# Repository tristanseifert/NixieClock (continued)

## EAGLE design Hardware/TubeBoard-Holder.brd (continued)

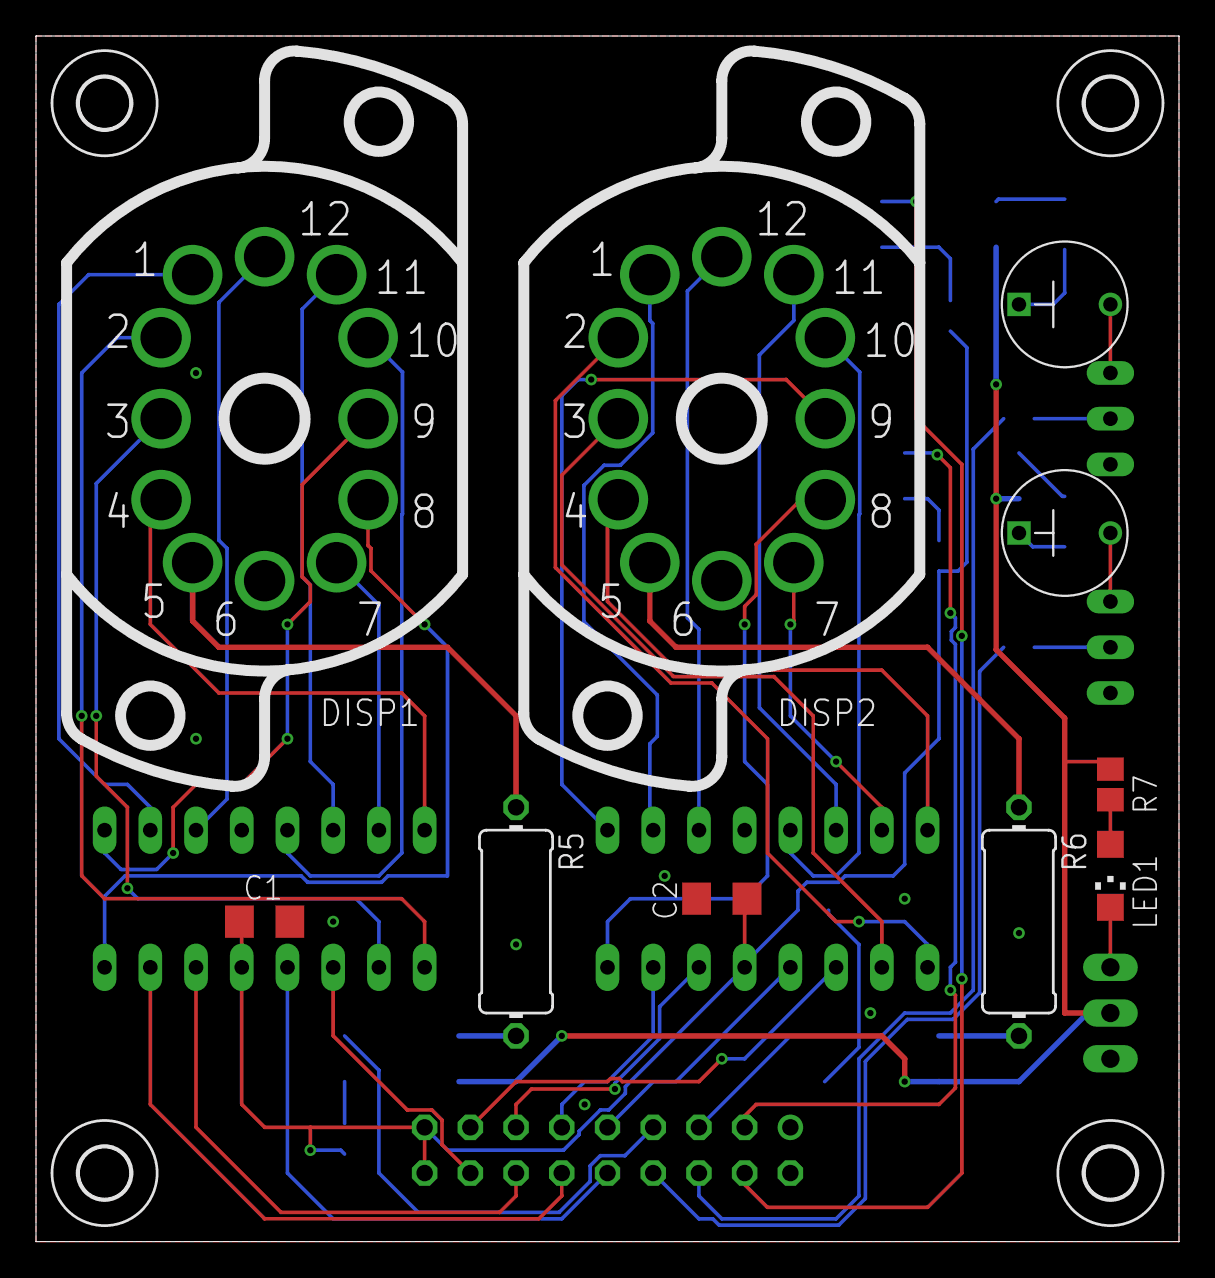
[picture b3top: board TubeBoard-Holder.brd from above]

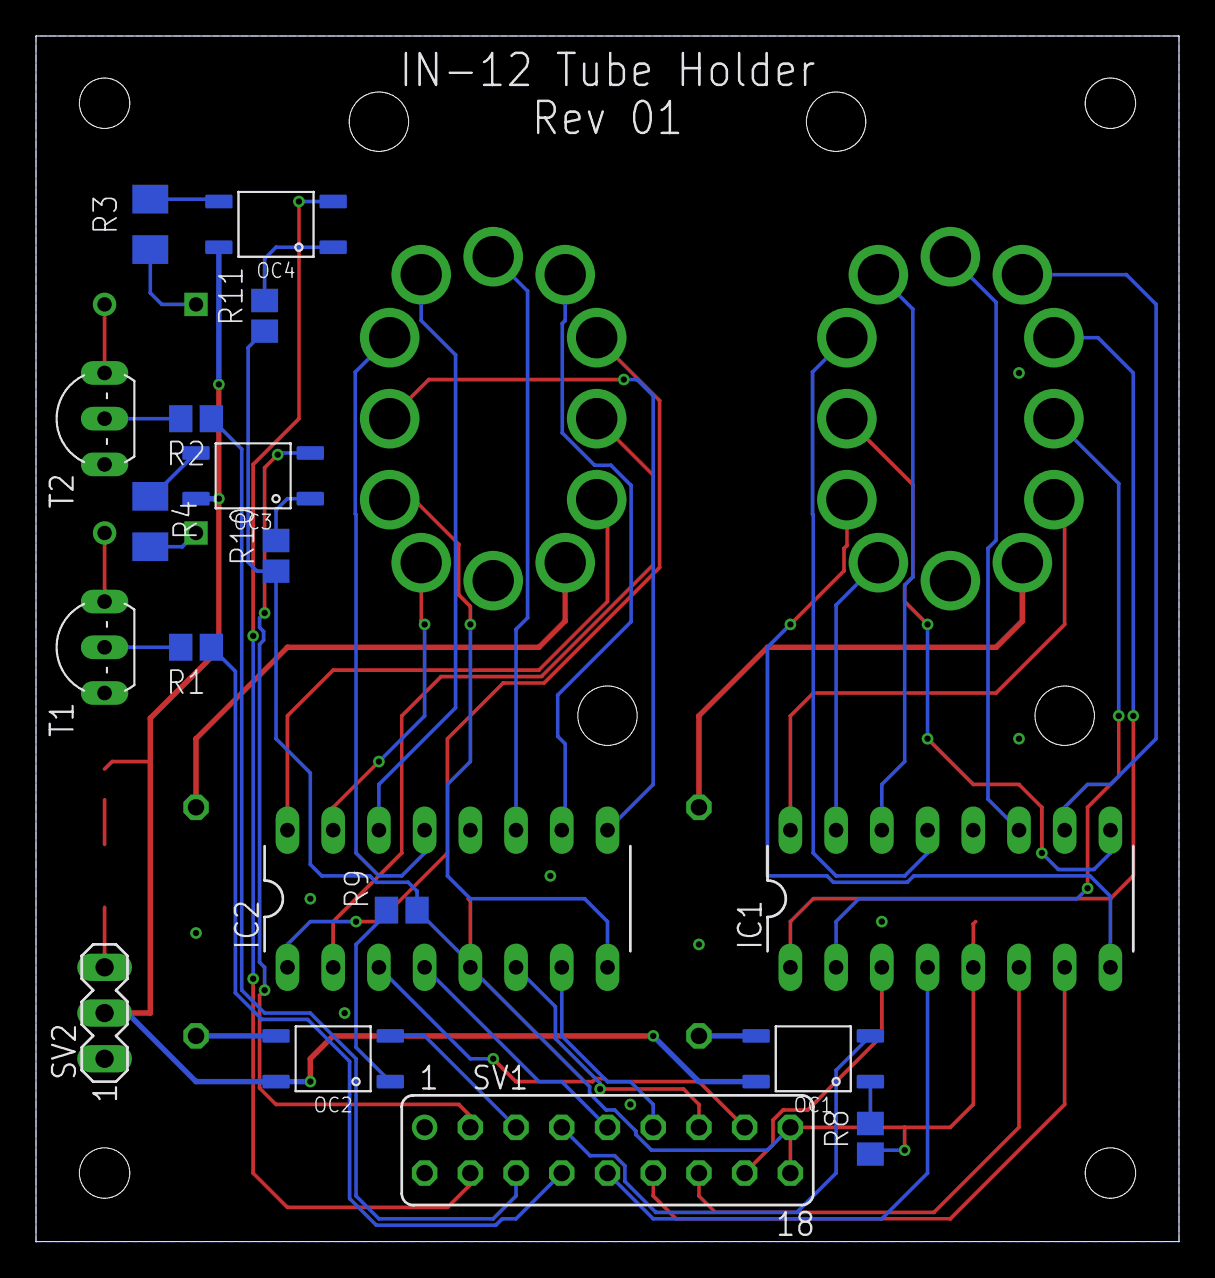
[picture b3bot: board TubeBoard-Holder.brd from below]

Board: 2 copper layers, 63.5 x 67.0 mm, 32 parts (18 on the bottom side), 54 nets.

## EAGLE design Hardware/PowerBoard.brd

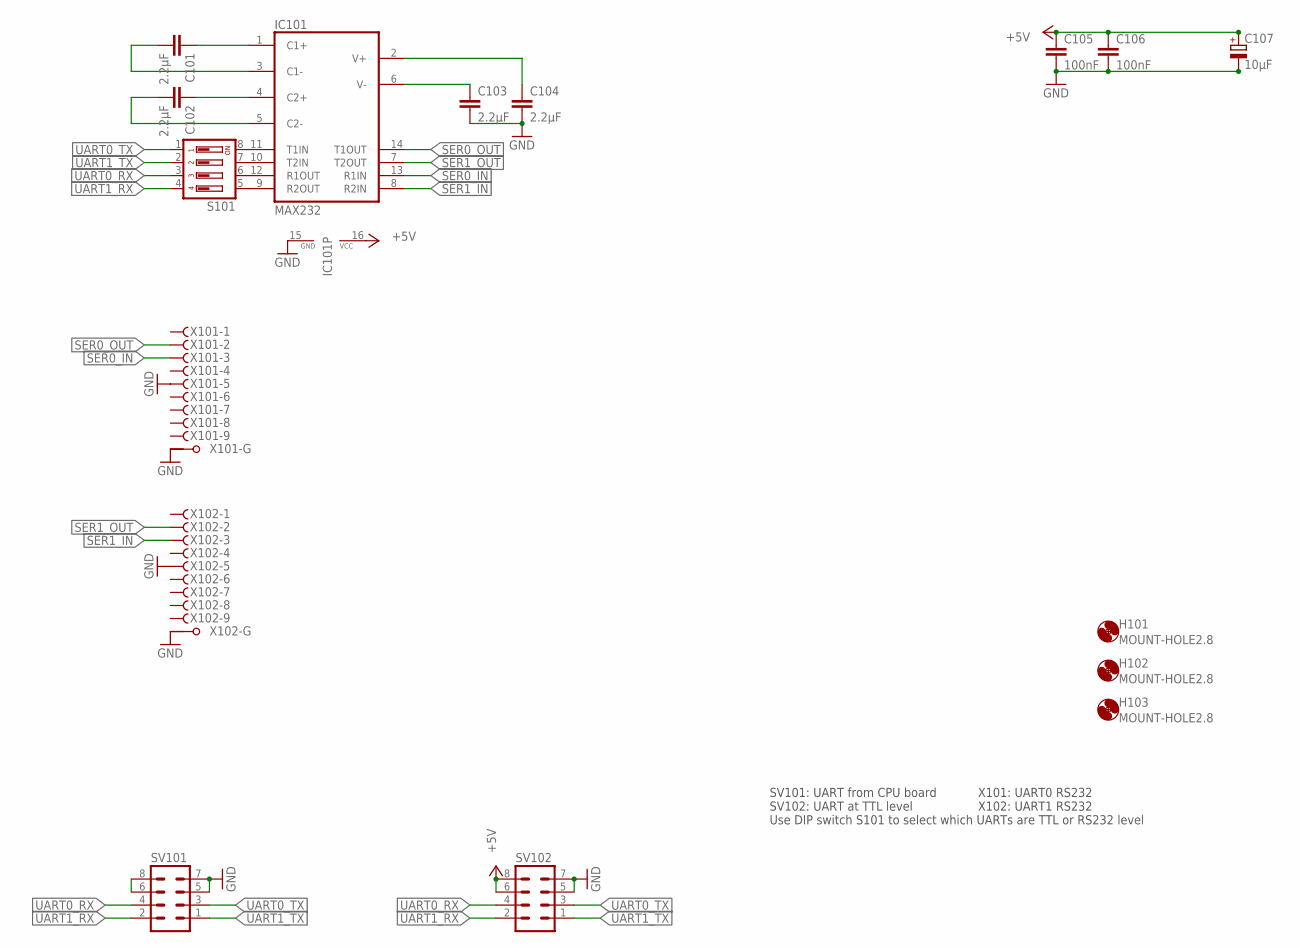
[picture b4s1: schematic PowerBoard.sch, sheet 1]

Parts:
C101, C102, C103, C104: 2.2µF; C0805; MOUSER 710-885012107016
C105, C106: 100nF; C0805; MOUSER 710-885012207072
C107: 10µF; SMC_B; MOUSER 581-TAJB106K020RNJV
H101, H102, H103: MOUNT-HOLE2.8; 2,8
IC101: MAX232; DIL16; MOUSER 595-MAX232N
S101: DP04; DP-04; MOUSER 611-BDB04
SV101, SV102: MA04-2
X101, X102: F09HPS; F09HP

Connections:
+5V: C105.1, C106.1, C107.+, IC101.16 (VCC), SV102.6, SV102.8; also elsewhere on the board
GND: C103.2, C104.2, C105.2, C106.2, C107.-, IC101.15 (GND), SV101.5, SV101.7, SV102.5, SV102.7, X101.5 (F), X101.G1, X102.5 (F), X102.G1; also elsewhere on the board
unnamed: C104.1, IC101.2 (V+)
unnamed: C103.1, IC101.6 (V-)
unnamed: C102.1, IC101.4 (C2+)
unnamed: C101.1, IC101.1 (C1+)
unnamed: SV101.6, SV101.8
unnamed: IC101.9 (R2OUT), S101.5
unnamed: C102.2, IC101.5 (C2-)
unnamed: C101.2, IC101.3 (C1-)
unnamed: IC101.12 (R1OUT), S101.6
unnamed: IC101.10 (T2IN), S101.7
unnamed: IC101.11 (T1IN), S101.8
SER0_IN: IC101.13 (R1IN), X101.3 (F)
SER0_OUT: IC101.14 (T1OUT), X101.2 (F)
SER1_IN: IC101.8 (R2IN), X102.3 (F)
SER1_OUT: IC101.7 (T2OUT), X102.2 (F)
UART0_RX: S101.3, SV101.4, SV102.4
UART0_TX: S101.1, SV101.3, SV102.3
UART1_RX: S101.4, SV101.2, SV102.2
UART1_TX: S101.2, SV101.1, SV102.1

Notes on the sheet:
X101: UART0 RS232 X102: UART1 RS232
SV101: UART from CPU board SV102: UART at TTL level Use DIP switch S101 to select which UARTs are TTL or RS232 level

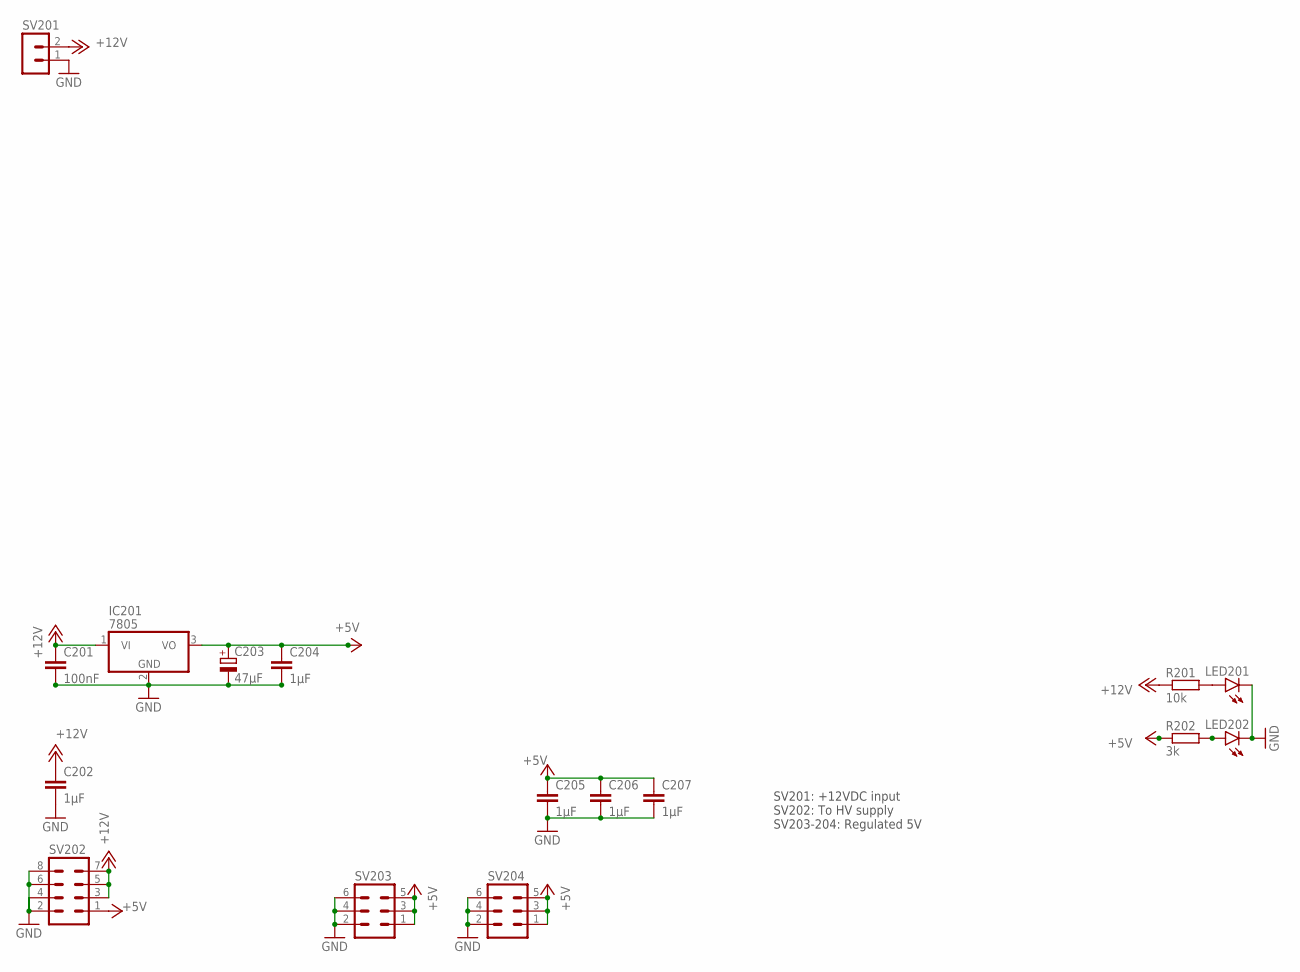
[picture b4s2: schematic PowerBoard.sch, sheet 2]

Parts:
C201: 100nF; C0805; MOUSER 710-885012207072
C202, C204, C205, C206, C207: 1µF; C0805; MOUSER 710-885012107015
C203: 47µF; CT6032; MOUSER 581-TAJD476M016RNJV
IC201: 7805; TO220V; MOUSER 490-VXO7805-1000
LED201, LED202: LEDCHIPLED_1206; CHIPLED_1206; MOUSER 710-156120YS75300
R201: 10k; R2012; MOUSER 652-CR0805FX-1002ELF
R202: 3k; R2012; MOUSER 652-CR0805JW-302ELF
SV201: 1792863
SV202: MA04-2
SV203, SV204: MA03-2

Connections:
+5V: C203.+, C204.1, C205.1, C206.1, C207.1, IC201.3 (VO), R202.1, SV202.1, SV203.1, SV203.3, SV203.5, SV204.1, SV204.3, SV204.5; also elsewhere on the board
+12V: C201.1, C202.1, IC201.1 (VI), R201.1, SV201.2, SV202.3, SV202.5, SV202.7
GND: C201.2, C202.2, C203.-, C204.2, C205.2, C206.2, C207.2, IC201.2 (GND), LED201.C, LED202.C, SV201.1, SV202.2, SV202.4, SV202.6, SV202.8, SV203.2, SV203.4, SV203.6, SV204.2, SV204.4, SV204.6; also elsewhere on the board
unnamed: LED202.A, R202.2
unnamed: LED201.A, R201.2

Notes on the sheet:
SV201: +12VDC input SV202: To HV supply SV203-204: Regulated 5V

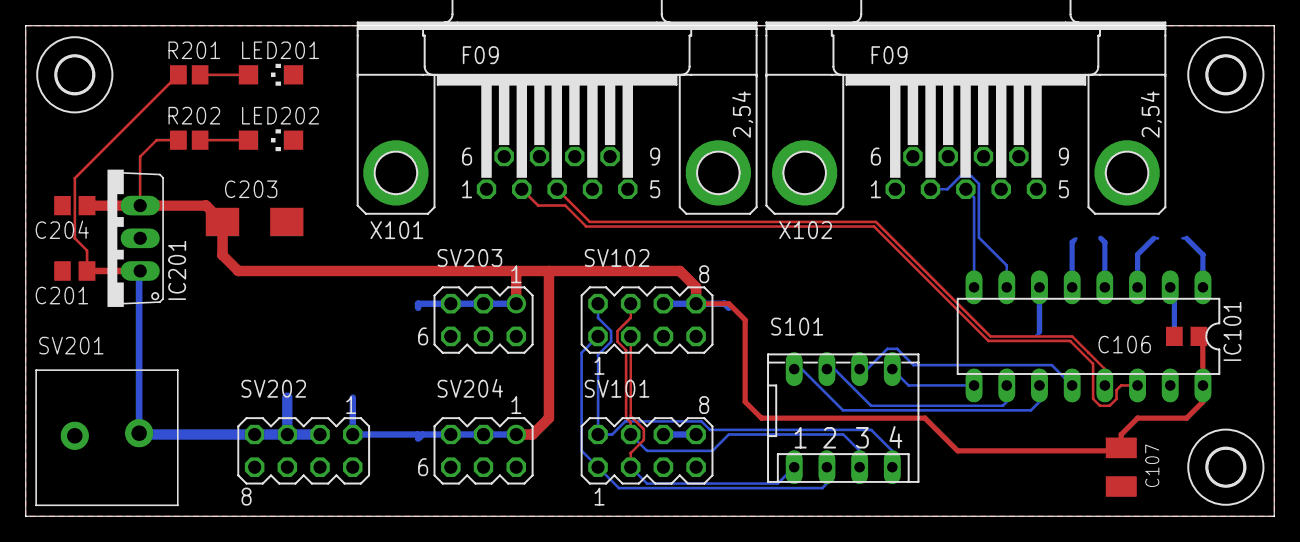
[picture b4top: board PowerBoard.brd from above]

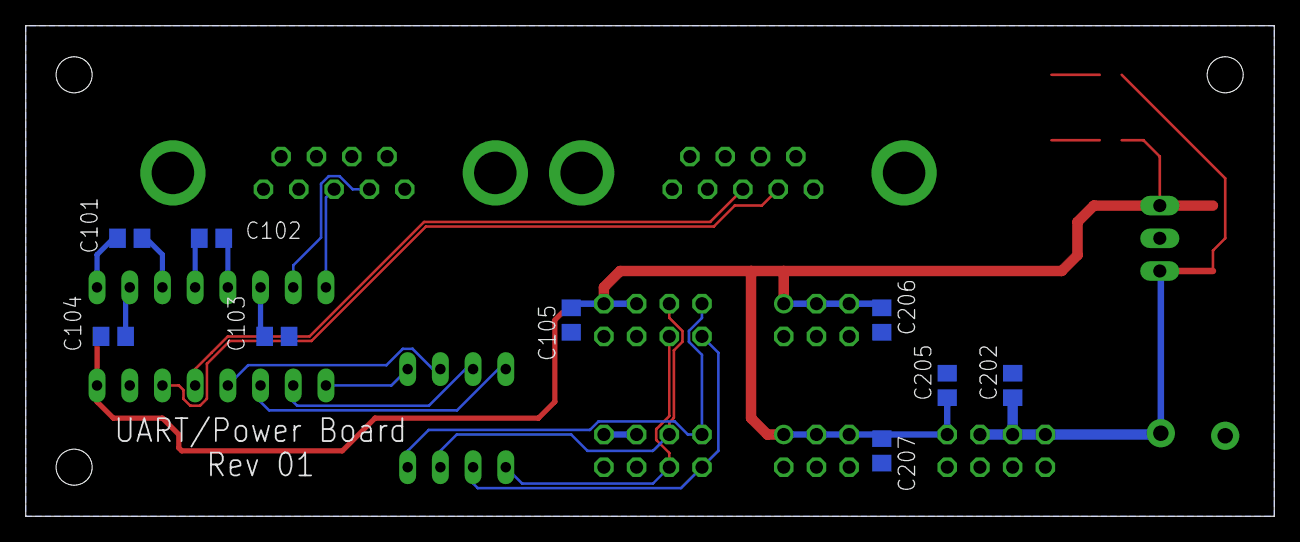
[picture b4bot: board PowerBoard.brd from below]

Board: 2 copper layers, 97.0 x 38.1 mm, 32 parts (9 on the bottom side), 24 nets.

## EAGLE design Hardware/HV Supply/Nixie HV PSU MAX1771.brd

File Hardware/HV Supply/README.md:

# Nixie Clock HV Supply
This power supply is based on Nick de Smith's [Nixie HV Switching PSU](https://www.desmith.net/NMdS/Electronics/NixiePSU.html) and derived from the provided EAGLE files. Modifications were made to use different connectors, and to add Mouser part numbers.

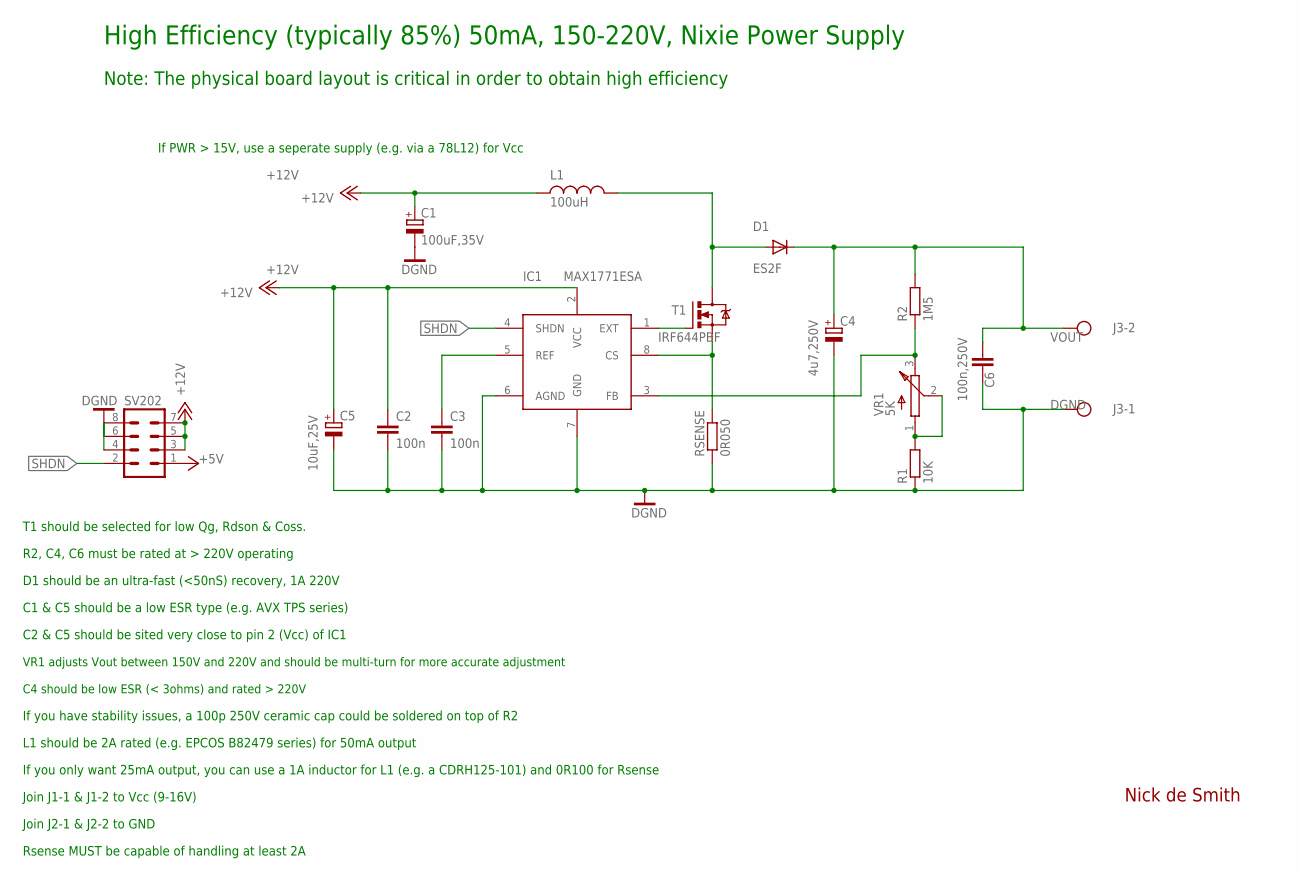
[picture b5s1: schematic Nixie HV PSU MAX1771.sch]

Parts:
C1: 100uF,35V; C-EIA-7343; MOUSER 581-TPSD107M020R0085
C2, C3: 100n; C0805; MOUSER 80-C0805C104M4V
C4: 4u7,250V; NICHICON-UJ-12; MOUSER 667-EEV-EB2E100Q
C5: 10uF,25V; C-EIA-7343; MOUSER 581-TPSD106K035R0300
C6: 100n,250V; C2420; MOUSER 667-ECW-U2104KC9
D1: ES2F; SMC; MOUSER 821-ES2FR5
IC1: MAX1771ESA; SO-8; MOUSER 700-MAX1771ESAT
J3: TERM-BLOCK-2-02IN; SCREW-2-02
L1: 100uH; L-B82479; MOUSER 871-B82479A1104M
R1: 10K; R0805; MOUSER 71-CRCW080510K0FKEAC
R2: 1M5; R2512; MOUSER 279-35221M5JT
RSENSE: 0R050; R2010; MOUSER 66-LR2010LF-01-R050
SV202: MA04-2
T1: IRF644PBF; TO220BV; MOUSER 844-IRF644PBF
VR1: 5K; BOURNS-3214W; MOUSER 652-3214W-1-502E

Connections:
+5V: SV202.1
+12V: C1.+, C2.1, C5.+, IC1.2 (VCC), L1.P$1 (1), SV202.3, SV202.5, SV202.7
DGND: C1.-, C2.2, C3.2, C4.1 (-), C5.-, C6.P$2 (2), IC1.6 (AGND), IC1.7 (GND), J3.1, R1.1, RSENSE.1, SV202.4, SV202.6, SV202.8
EXT: IC1.1 (EXT), T1.G
unnamed: IC1.8 (CS), RSENSE.2, T1.S
unnamed: R1.2, VR1.1 (A), VR1.2 (W)
unnamed: IC1.3 (FB), R2.1, VR1.3 (B)
unnamed: D1.A, L1.P$2 (2), T1.D
unnamed: C3.1, IC1.5 (REF)
SHDN: IC1.4 (SHDN), SV202.2
VOUT: C4.2 (+), C6.P$1 (1), D1.C, J3.2, R2.2

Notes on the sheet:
R2, C4, C6 must be rated at > 220V operating
D1 should be an ultra-fast (<50nS) recovery, 1A 220V
C1 & C5 should be a low ESR type (e.g. AVX TPS series)
C2 & C5 should be sited very close to pin 2 (Vcc) of IC1
Nick de Smith
VR1 adjusts Vout between 150V and 220V and should be multi-turn for more accurate adjustment
C4 should be low ESR (< 3ohms) and rated > 220V
If you have stability issues, a 100p 250V ceramic cap could be soldered on top of R2
L1 should be 2A rated (e.g. EPCOS B82479 series) for 50mA output
Join J1-1 & J1-2 to Vcc (9-16V)
Join J2-1 & J2-2 to GND
T1 should be selected for low Qg, Rdson & Coss.
Rsense MUST be capable of handling at least 2A
High Efficiency (typically 85%) 50mA, 150-220V, Nixie Power Supply
If PWR > 15V, use a seperate supply (e.g. via a 78L12) for Vcc
Note: The physical board layout is critical in order to obtain high efficiency
If you only want 25mA output, you can use a 1A inductor for L1 (e.g. a CDRH125-101) and 0R100 for Rsense

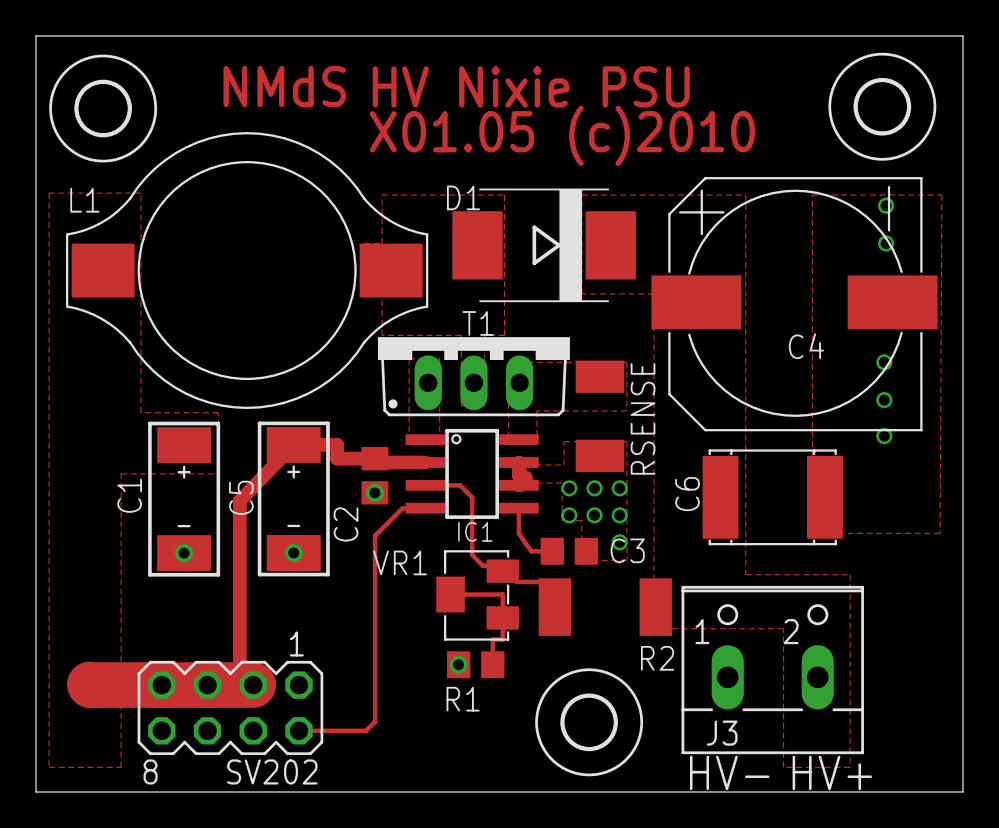
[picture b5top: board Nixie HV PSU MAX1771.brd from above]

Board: 2 copper layers, 51.5 x 42.0 mm, 19 parts (0 on the bottom side), 10 nets.

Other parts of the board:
U$2, U$3, U$4: 2,8

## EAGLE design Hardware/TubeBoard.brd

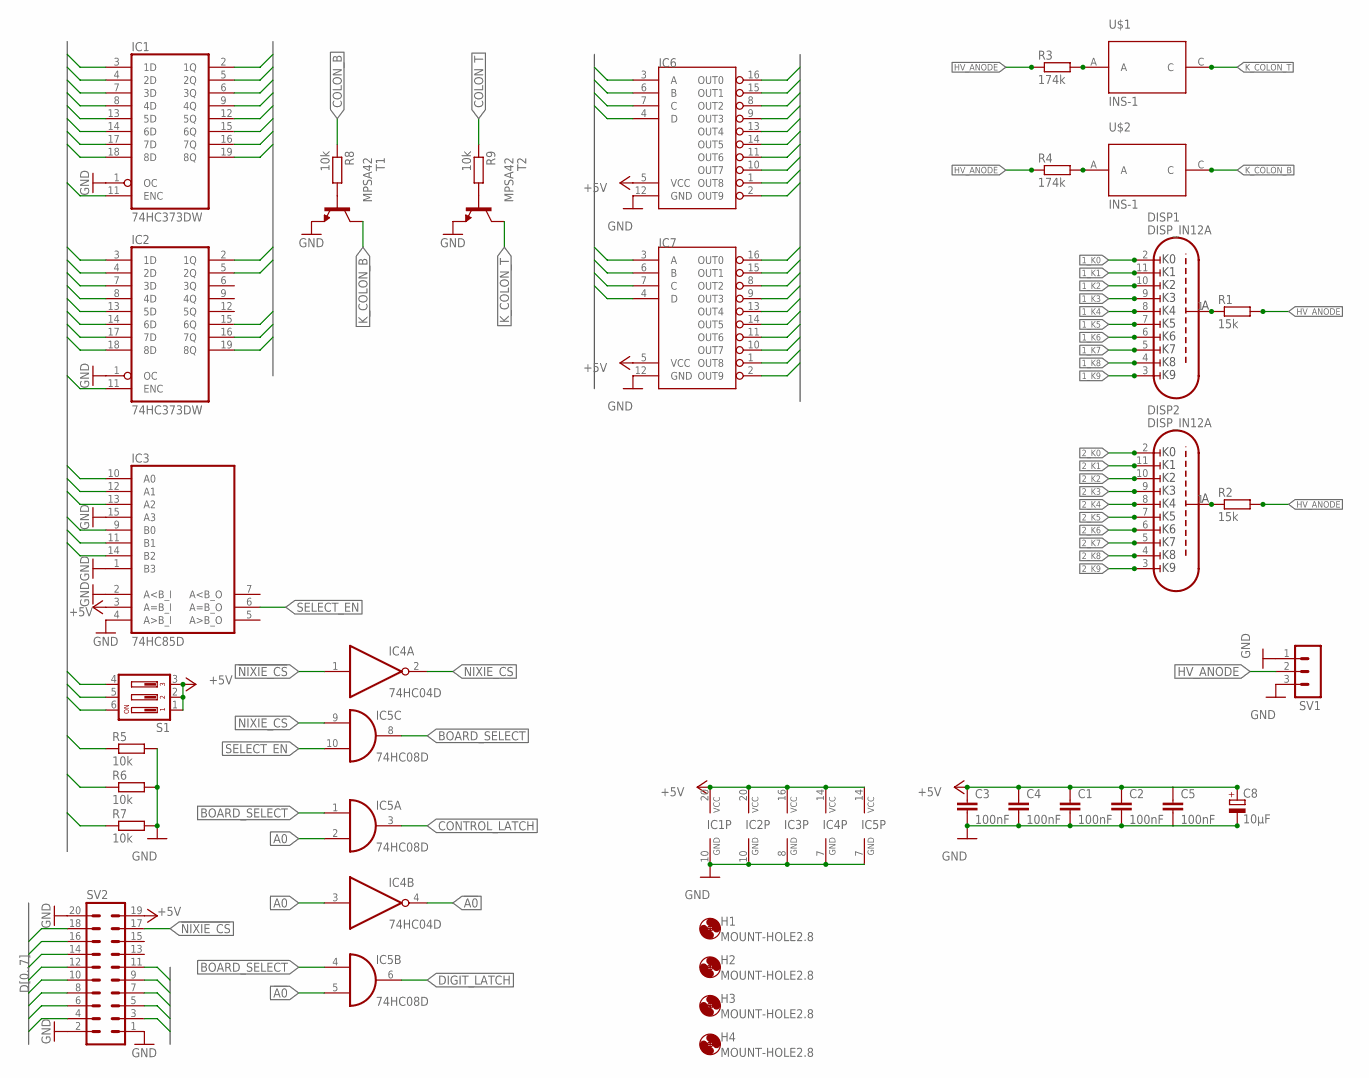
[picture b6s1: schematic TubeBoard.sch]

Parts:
C1, C2, C3, C4, C5: 100nF; C1206
C8: 10µF; SMC_B; MOUSER 581-TAJB106K020RNJV
DISP1, DISP2: DISP_IN12A; DISP_IN-12_SOCKET
H1, H2, H3, H4: MOUNT-HOLE2.8; 2,8
IC1, IC2: 74HC373DW; SO20W
IC3: 74HC85D; SO16; MOUSER 771-74HC85D-T
IC4: 74HC04D; SO14
IC5: 74HC08D; SO14
IC6, IC7: 7441DIL16; DIL16
R1, R2: 15k; 0411/12
R3, R4: 174k; M1206; MOUSER 667-ERJ-8ENF1743V
R5, R6, R7, R8, R9: 10k; R2012; MOUSER 652-CR0805FX-1002ELF
S1: SD4-03; MOUSER 611-BDB03
SV1: MA03-1
SV2: MA10-2
T1, T2: MPSA42; TO92-EBC; MOUSER 833-MPSA42-AP
U$1, U$2: INS-1

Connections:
1_K0: DISP1.2 (K0), IC6.16 (OUT0)
1_K1: DISP1.11 (K1), IC6.15 (OUT1)
1_K2: DISP1.10 (K2), IC6.8 (OUT2)
1_K3: DISP1.9 (K3), IC6.9 (OUT3)
1_K4: DISP1.8 (K4), IC6.13 (OUT4)
1_K5: DISP1.7 (K5), IC6.14 (OUT5)
1_K6: DISP1.6 (K6), IC6.11 (OUT6)
1_K7: DISP1.5 (K7), IC6.10 (OUT7)
1_K8: DISP1.4 (K8), IC6.1 (OUT8)
1_K9: DISP1.3 (K9), IC6.2 (OUT9)
2_K0: DISP2.2 (K0), IC7.16 (OUT0)
2_K1: DISP2.11 (K1), IC7.15 (OUT1)
2_K2: DISP2.10 (K2), IC7.8 (OUT2)
2_K3: DISP2.9 (K3), IC7.9 (OUT3)
2_K4: DISP2.8 (K4), IC7.13 (OUT4)
2_K5: DISP2.7 (K5), IC7.14 (OUT5)
2_K6: DISP2.6 (K6), IC7.11 (OUT6)
2_K7: DISP2.5 (K7), IC7.10 (OUT7)
2_K8: DISP2.4 (K8), IC7.1 (OUT8)
2_K9: DISP2.3 (K9), IC7.2 (OUT9)
!A0: IC4.4 (O), IC5.5 (I1)
!NIXIE_CS: IC4.1 (I), SV2.17
+5V: C1.1, C2.1, C3.1, C4.1, C5.1, C8.+, IC1.20 (VCC), IC2.20 (VCC), IC3.3 (A=B_I), IC3.16 (VCC), IC4.14 (VCC), IC5.14 (VCC), IC6.5 (VCC), IC7.5 (VCC), S1.1, S1.2, S1.3, SV2.19
A0: IC4.3 (I), IC5.2 (I1), SV2.3
A1: SV2.5
A2: IC3.10 (A0), SV2.7
A3: IC3.12 (A1), SV2.9
A4: IC3.13 (A2), SV2.11
BOARD_SELECT: IC5.1 (I0), IC5.4 (I0), IC5.8 (O)
COLON_B: IC2.2 (1Q), R8.1
COLON_T: IC2.5 (2Q), R9.1
CONTROL_LATCH: IC2.11 (ENC), IC5.3 (O)
D0: IC1.3 (1D), IC2.3 (1D), SV2.8
D1: IC1.4 (2D), IC2.4 (2D), SV2.6
D2: IC1.7 (3D), IC2.7 (3D), SV2.4
D3: IC1.8 (4D), IC2.8 (4D), SV2.10
D4: IC1.13 (5D), IC2.13 (5D), SV2.12
D5: IC1.14 (6D), IC2.14 (6D), SV2.14
D6: IC1.17 (7D), IC2.17 (7D), SV2.16
D7: IC1.18 (8D), IC2.18 (8D), SV2.18
DIGIT_LATCH: IC1.11 (ENC), IC5.6 (O)
DRIVE_HI: IC2.19 (8Q)
DRIVE_LO: IC2.15 (6Q)
DRIVE_MED: IC2.16 (7Q)
GND: C1.2, C2.2, C3.2, C4.2, C5.2, C8.-, IC1.1 (OC), IC1.10 (GND), IC2.1 (OC), IC2.10 (GND), IC3.1 (B3), IC3.2 (A<B_I), IC3.4 (A>B_I), IC3.8 (GND), IC3.15 (A3), IC4.7 (GND), IC5.7 (GND), IC6.12 (GND), IC7.12 (GND), R5.2, R6.2, R7.2, SV1.1, SV1.3, SV2.1, SV2.2, SV2.20, T1.E, T2.E
HV_ANODE: R1.2, R2.2, R3.1, R4.1, SV1.2
ID0: IC3.9 (B0), R7.1, S1.6
ID1: IC3.11 (B1), R6.1, S1.5
ID2: IC3.14 (B2), R5.1, S1.4
K_COLON_B: T1.C, U$2.C
K_COLON_T: T2.C, U$1.C
LDIGIT0: IC1.2 (1Q), IC6.3 (A)
LDIGIT1: IC1.5 (2Q), IC6.6 (B)
LDIGIT2: IC1.6 (3Q), IC6.7 (C)
LDIGIT3: IC1.9 (4Q), IC6.4 (D)
unnamed: DISP1.1 (ANODE), R1.1
unnamed: DISP2.1 (ANODE), R2.1
unnamed: R3.2, U$1.A
unnamed: R4.2, U$2.A
unnamed: R8.2, T1.B
unnamed: R9.2, T2.B
NIXIE_CS: IC4.2 (O), IC5.9 (I0)
RDIGIT0: IC1.12 (5Q), IC7.3 (A)
RDIGIT1: IC1.15 (6Q), IC7.6 (B)
RDIGIT2: IC1.16 (7Q), IC7.7 (C)
RDIGIT3: IC1.19 (8Q), IC7.4 (D)
SELECT_EN: IC3.6 (A=B_O), IC5.10 (I1)

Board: 2 copper layers, 35 parts (4 on the bottom side), 63 nets, no tracks yet.

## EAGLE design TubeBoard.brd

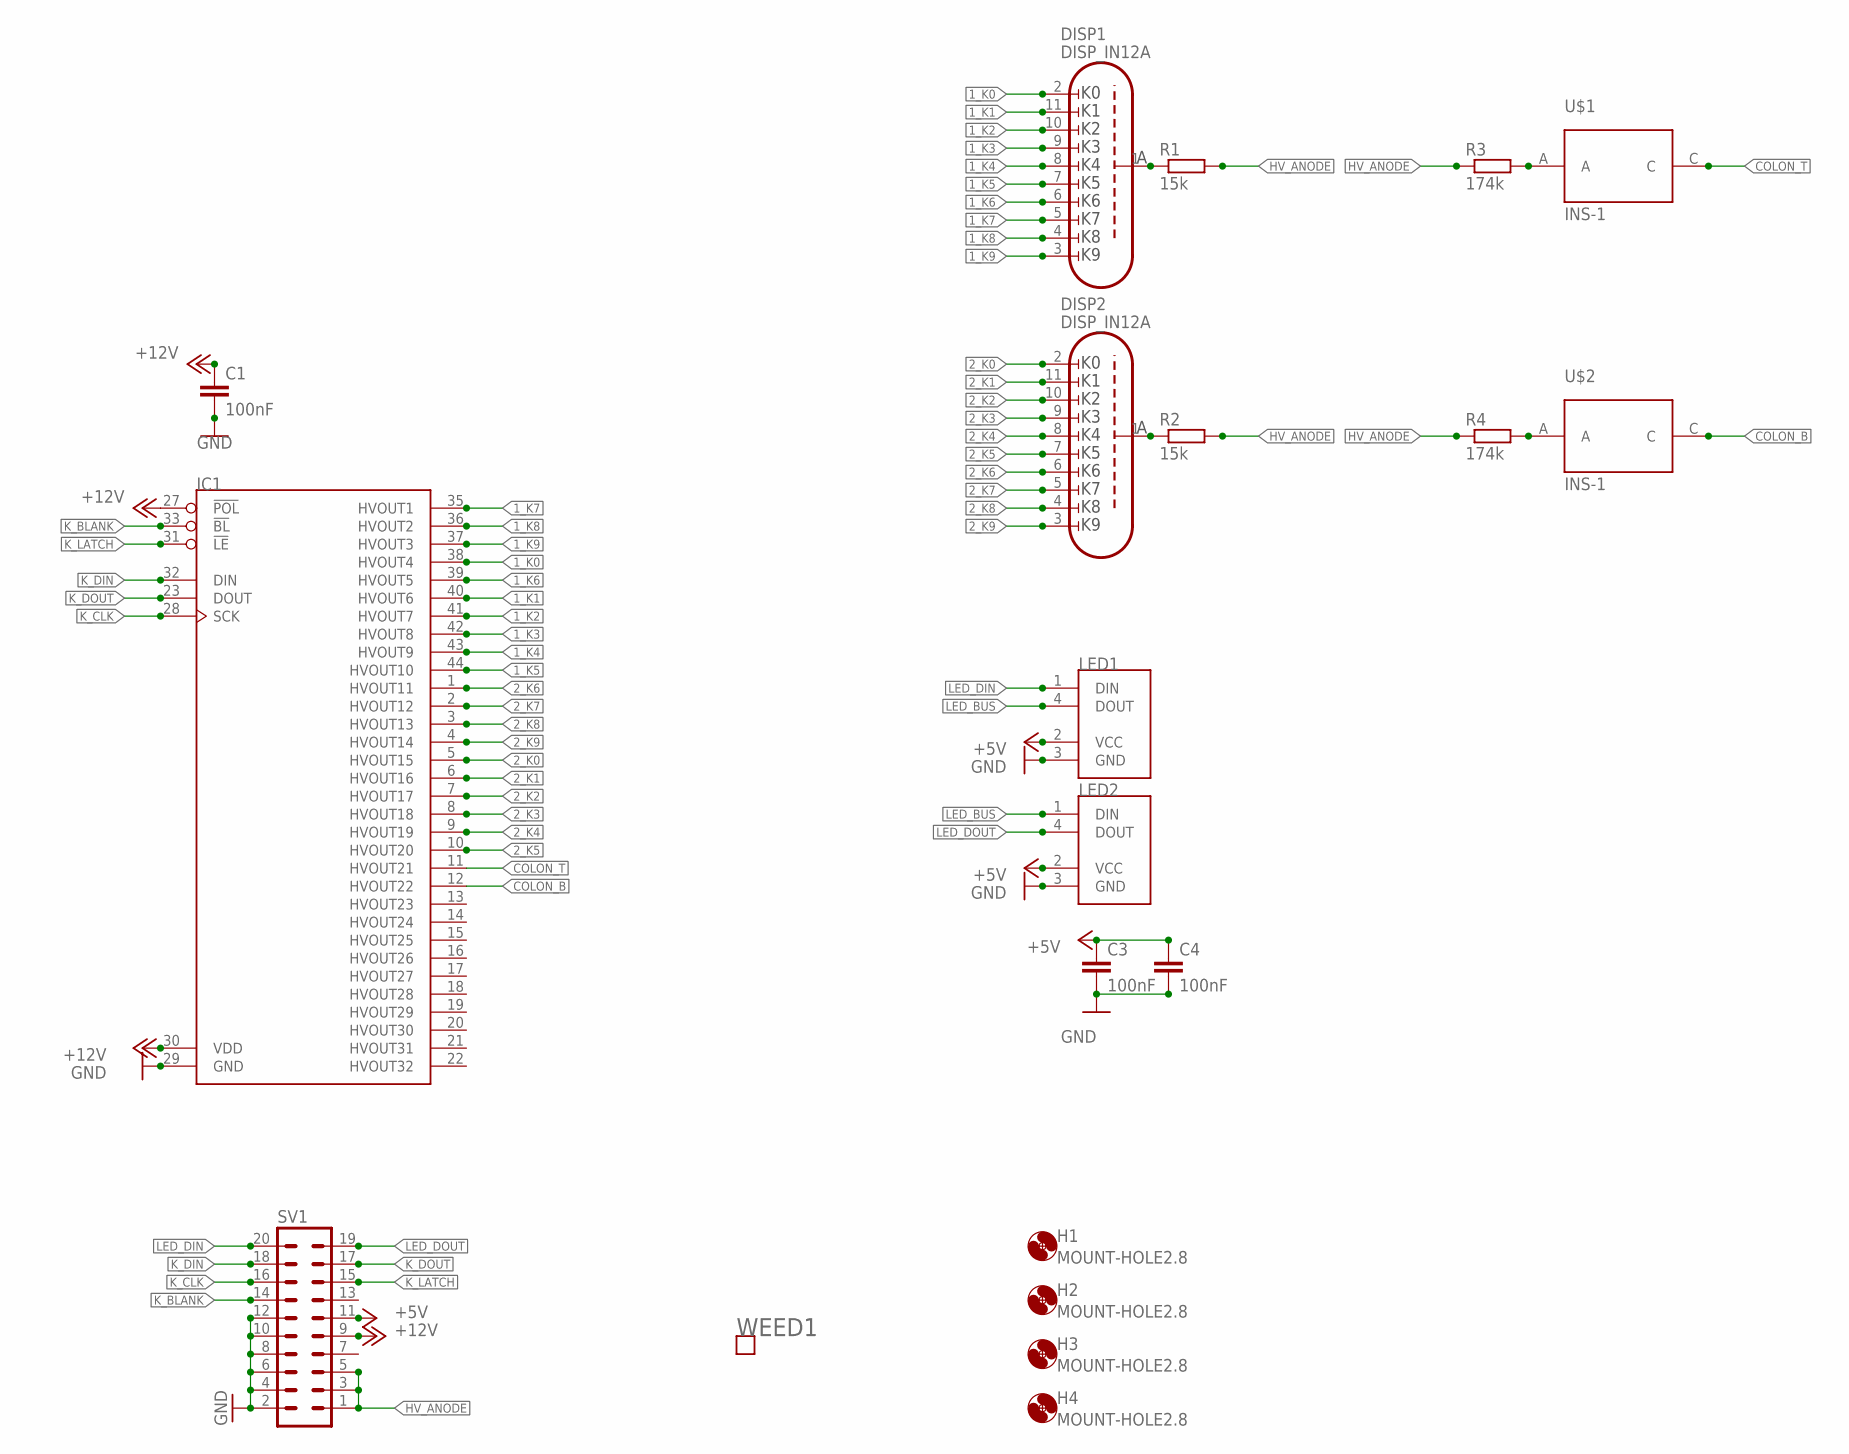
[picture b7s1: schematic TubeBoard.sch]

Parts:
C1, C3, C4: 100nF; C1206
DISP1, DISP2: DISP_IN12A; DISP_IN-12_SOCKET
H1, H2, H3, H4: MOUNT-HOLE2.8; 2,8
IC1: HV5530PQFP-44; PQFP44
LED1, LED2: NEOPIXEL-5MMLED-4PIN; LED5MMRGB
R1, R2: 15k; 0411/12
R3, R4: 174k; M1206; MOUSER 667-ERJ-8ENF1743V
SV1: MA10-2
U$1, U$2: INS-1
WEED1: WEED; DOINK

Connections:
1_K0: DISP1.2 (K0), IC1.38 (HVOUT4)
1_K1: DISP1.11 (K1), IC1.40 (HVOUT6)
1_K2: DISP1.10 (K2), IC1.41 (HVOUT7)
1_K3: DISP1.9 (K3), IC1.42 (HVOUT8)
1_K4: DISP1.8 (K4), IC1.43 (HVOUT9)
1_K5: DISP1.7 (K5), IC1.44 (HVOUT10)
1_K6: DISP1.6 (K6), IC1.39 (HVOUT5)
1_K7: DISP1.5 (K7), IC1.35 (HVOUT1)
1_K8: DISP1.4 (K8), IC1.36 (HVOUT2)
1_K9: DISP1.3 (K9), IC1.37 (HVOUT3)
2_K0: DISP2.2 (K0), IC1.5 (HVOUT15)
2_K1: DISP2.11 (K1), IC1.6 (HVOUT16)
2_K2: DISP2.10 (K2), IC1.7 (HVOUT17)
2_K3: DISP2.9 (K3), IC1.8 (HVOUT18)
2_K4: DISP2.8 (K4), IC1.9 (HVOUT19)
2_K5: DISP2.7 (K5), IC1.10 (HVOUT20)
2_K6: DISP2.6 (K6), IC1.1 (HVOUT11)
2_K7: DISP2.5 (K7), IC1.2 (HVOUT12)
2_K8: DISP2.4 (K8), IC1.3 (HVOUT13)
2_K9: DISP2.3 (K9), IC1.4 (HVOUT14)
!K_BLANK: IC1.33 (!BL), SV1.14
!K_LATCH: IC1.31 (!LE), SV1.15
+5V: C3.1, C4.1, LED1.2 (VCC), LED2.2 (VCC), SV1.11
+12V: C1.1, IC1.27 (!POL), IC1.30 (VDD), SV1.9
COLON_B: IC1.12 (HVOUT22), U$2.C
COLON_T: IC1.11 (HVOUT21), U$1.C
GND: C1.2, C3.2, C4.2, IC1.29 (GND), LED1.3 (GND), LED2.3 (GND), SV1.2, SV1.4, SV1.6, SV1.8, SV1.10, SV1.12
HV_ANODE: R1.2, R2.2, R3.1, R4.1, SV1.1, SV1.3, SV1.5
K_CLK: IC1.28 (SCK), SV1.16
K_DIN: IC1.32 (DIN), SV1.18
K_DOUT: IC1.23 (DOUT), SV1.17
LED_BUS: LED1.4 (DOUT), LED2.1 (DIN)
LED_DIN: LED1.1 (DIN), SV1.20
LED_DOUT: LED2.4 (DOUT), SV1.19
unnamed: DISP1.1 (ANODE), R1.1
unnamed: DISP2.1 (ANODE), R2.1
unnamed: R3.2, U$1.A
unnamed: R4.2, U$2.A

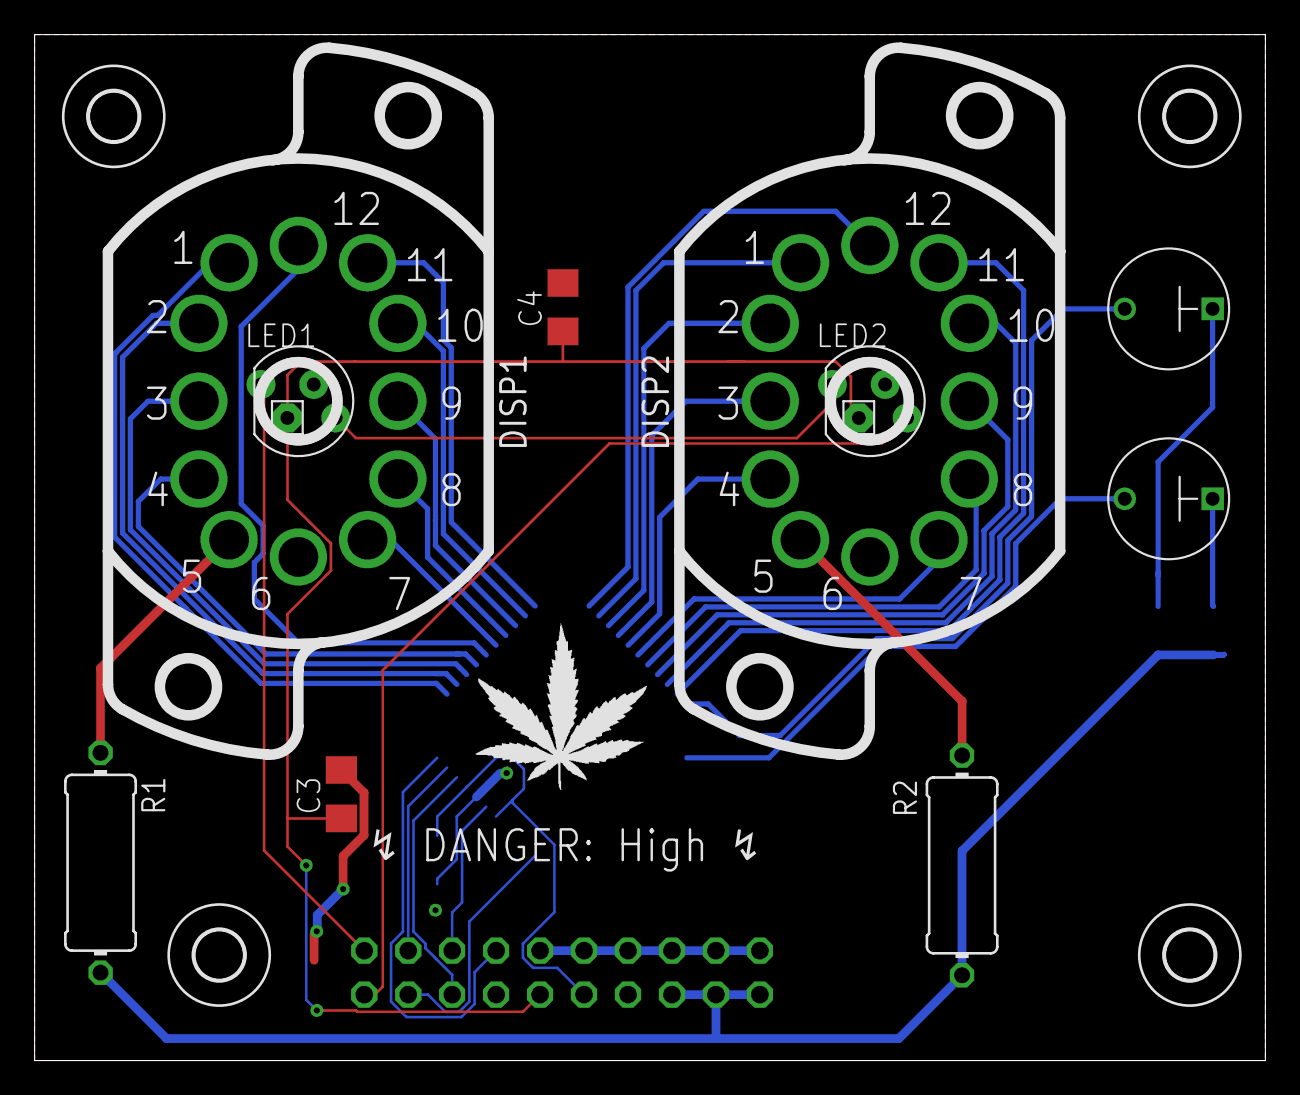
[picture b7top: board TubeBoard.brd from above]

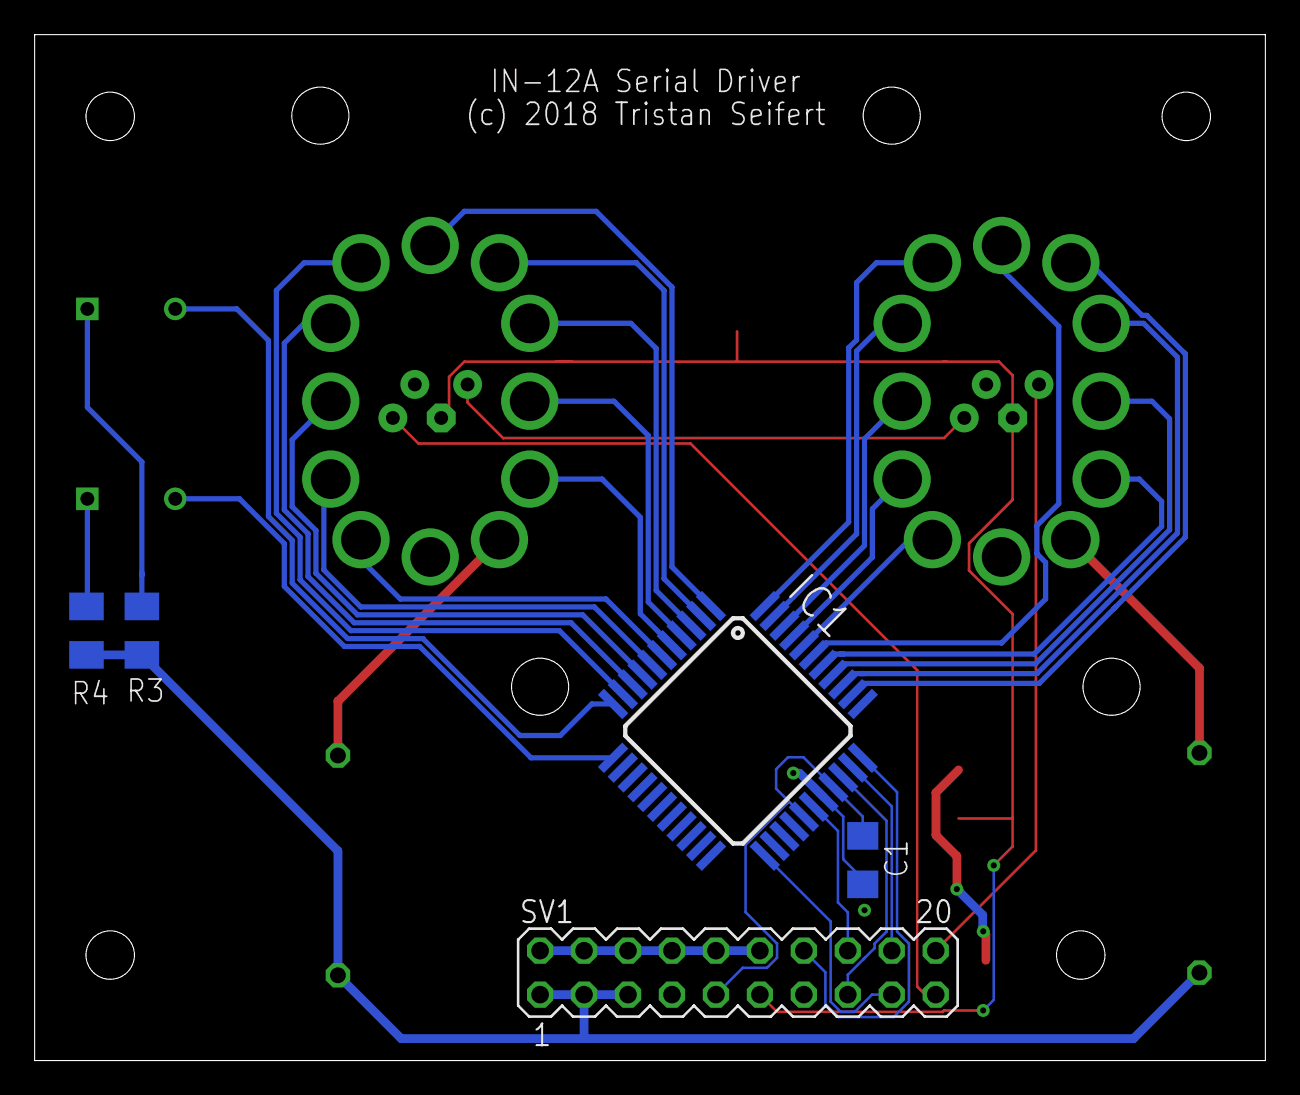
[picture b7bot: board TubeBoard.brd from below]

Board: 2 copper layers, 71.1 x 59.3 mm, 20 parts (5 on the bottom side), 38 nets.
